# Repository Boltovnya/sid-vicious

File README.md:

# SID Vicious

SID Vicious is an open source breakout board for the MOS 6582/8580 Sound Interface Device.

## Images

### PCB Front

### PCB Rear

## Schematic

The schematic for SID Vicious can be found [here](pdfs/SID%20Tester.pdf)

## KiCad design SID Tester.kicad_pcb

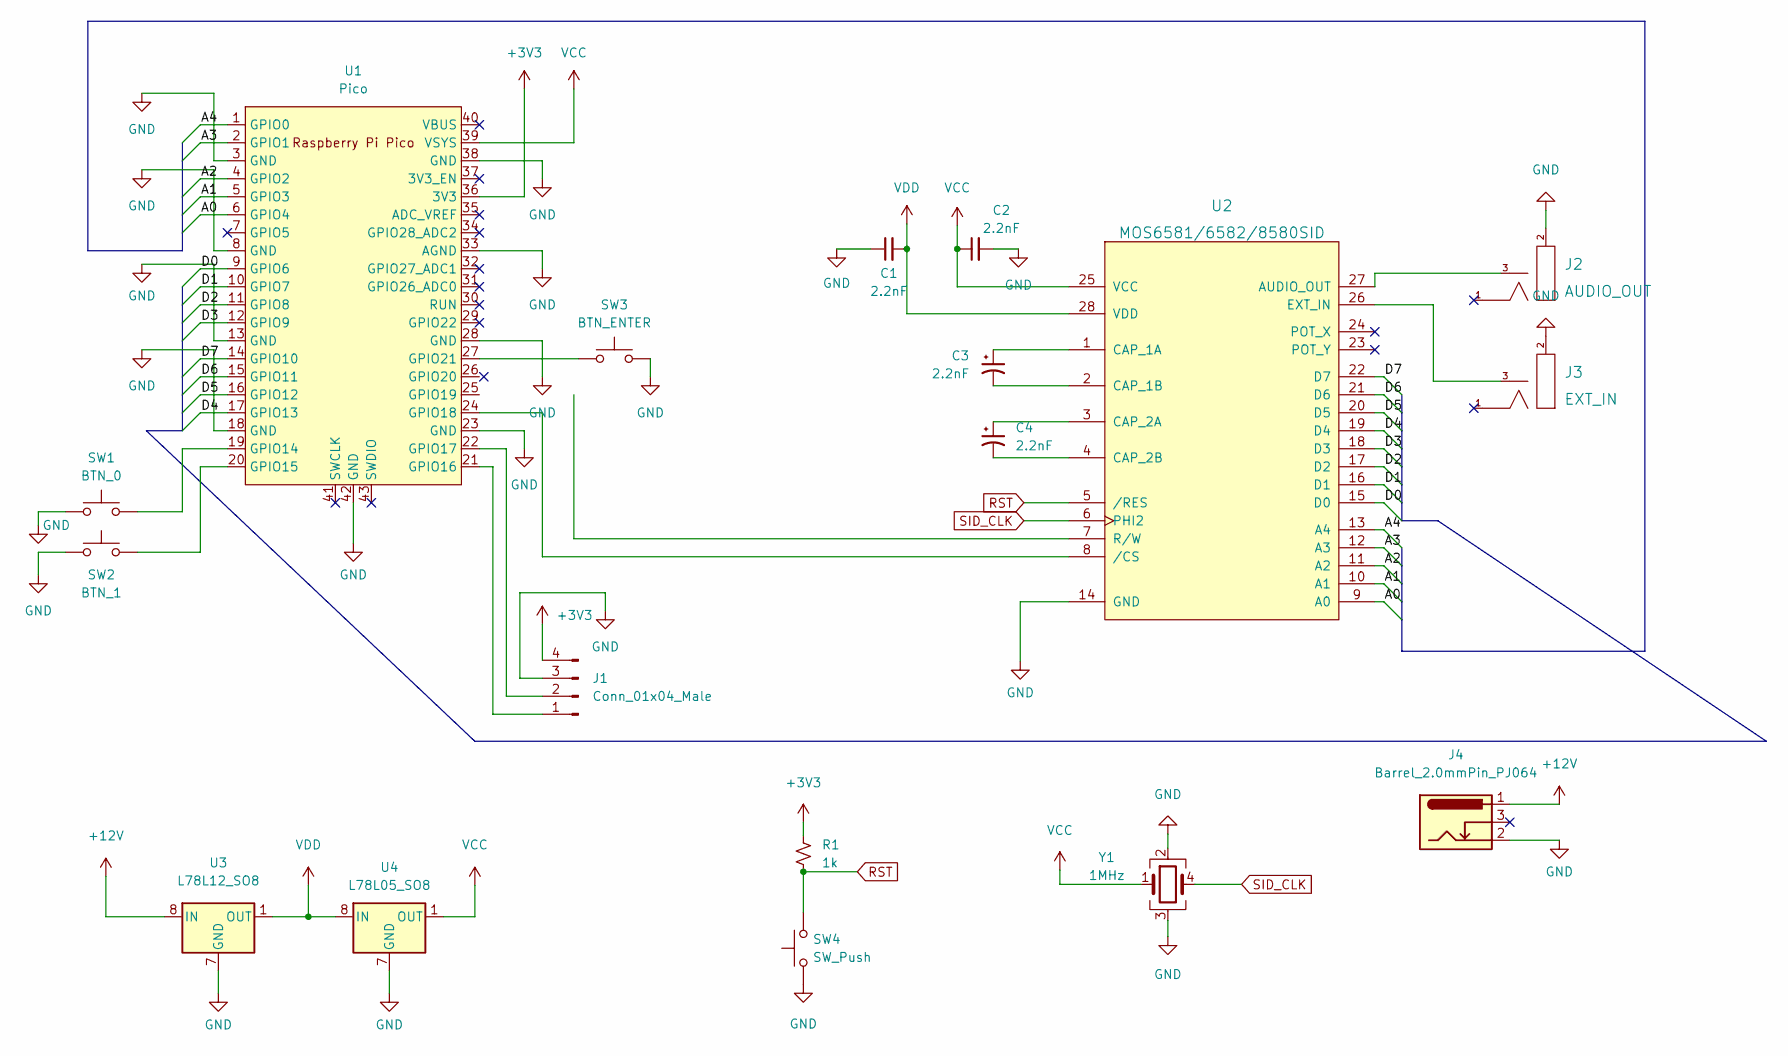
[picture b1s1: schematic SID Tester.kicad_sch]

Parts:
C1, C2: 2.2nF; C_0603_1608Metric
C3, C4: 2.2nF; CP_Elec_4x3
J1: Conn_01x04_Male; PinHeader_1x04_P1.27mm_Vertical
J2: AUDIO_OUT; EighthInch_PJ398SM; Part Number WQP-WQP518MA
J3: EXT_IN; EighthInch_PJ398SM; Part Number WQP-WQP518MA
J4: Barrel_2.0mmPin_PJ064; Barrel_Vert_PJ064_slotted; Part Number WQP-DC026M (2.0mm center pin)
R1: 1k; R_0603_1608Metric
SW1: BTN_0; SW_Cherry_MX_1.00u_PCB
SW2: BTN_1; SW_Cherry_MX_1.00u_PCB
SW3: BTN_ENTER; SW_Cherry_MX_1.00u_PCB
SW4: SW_Push; SW_SPST_EVQQ2
U1: Pico; RPi_Pico_SMD_TH
U2: MOS6581/6582/8580SID; DIP-28_W15.24mm_Socket
U3: L78L12_SO8; SOIC-8_3.9x4.9mm_P1.27mm
U4: L78L05_SO8; SOIC-8_3.9x4.9mm_P1.27mm
Y1: 1MHz; Crystal_SMD_TXC_7M-4Pin_3.2x2.5mm

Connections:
+3V3: J1.4, R1.1, U1.36 (3V3)
+12V: J4.1, U3.8 (IN)
/A0: U1.6 (GPIO4), U2.9 (A0)
/A1: U1.5 (GPIO3), U2.10 (A1)
/A2: U1.4 (GPIO2), U2.11 (A2)
/A3: U1.2 (GPIO1), U2.12 (A3)
/A4: U1.1 (GPIO0), U2.13 (A4)
/D0: U1.9 (GPIO6), U2.15 (D0)
/D1: U1.10 (GPIO7), U2.16 (D1)
/D2: U1.11 (GPIO8), U2.17 (D2)
/D3: U1.12 (GPIO9), U2.18 (D3)
/D4: U1.17 (GPIO13), U2.19 (D4)
/D5: U1.16 (GPIO12), U2.20 (D5)
/D6: U1.15 (GPIO11), U2.21 (D6)
/D7: U1.14 (GPIO10), U2.22 (D7)
GND: C1.1, C2.2, J1.3, J2.2 (SHEILD), J3.2 (SHEILD), J4.2, SW1.1, SW2.1, SW3.2, SW4.1, U1.3 (GND), U1.8 (GND), U1.13 (GND), U1.18 (GND), U1.23 (GND), U1.28 (GND), U1.33 (AGND), U1.38 (GND), U1.42 (GND), U2.14 (GND), U3.2 (GND), U3.3 (GND), U3.6 (GND), U3.7 (GND), U4.2 (GND), U4.3 (GND), U4.6 (GND), U4.7 (GND), Y1.2, Y1.3
unnamed: C3.1, U2.1 (CAP_1A)
unnamed: C3.2, U2.2 (CAP_1B)
unnamed: C4.1, U2.3 (CAP_2A)
unnamed: C4.2, U2.4 (CAP_2B)
unnamed: SW1.2, U1.19 (GPIO14)
unnamed: SW2.2, U1.20 (GPIO15)
unnamed: SW3.1, U1.27 (GPIO21)
unnamed: J1.1, U1.21 (GPIO16)
unnamed: J1.2, U1.22 (GPIO17)
unnamed: U1.24 (GPIO18), U2.8 (/CS)
unnamed: U1.25 (GPIO19), U2.7 (R/W)
unnamed: J3.3 (SW), U2.26 (EXT_IN)
unnamed: J2.3 (SW), U2.27 (AUDIO_OUT)
RST: R1.2, SW4.2, U2.5 (/RES)
SID_CLK: U2.6 (PHI2), Y1.4
VCC: C2.1, U1.39 (VSYS), U2.25 (VCC), U4.1 (OUT), Y1.1
VDD: C1.2, U2.28 (VDD), U3.1 (OUT), U4.8 (IN)

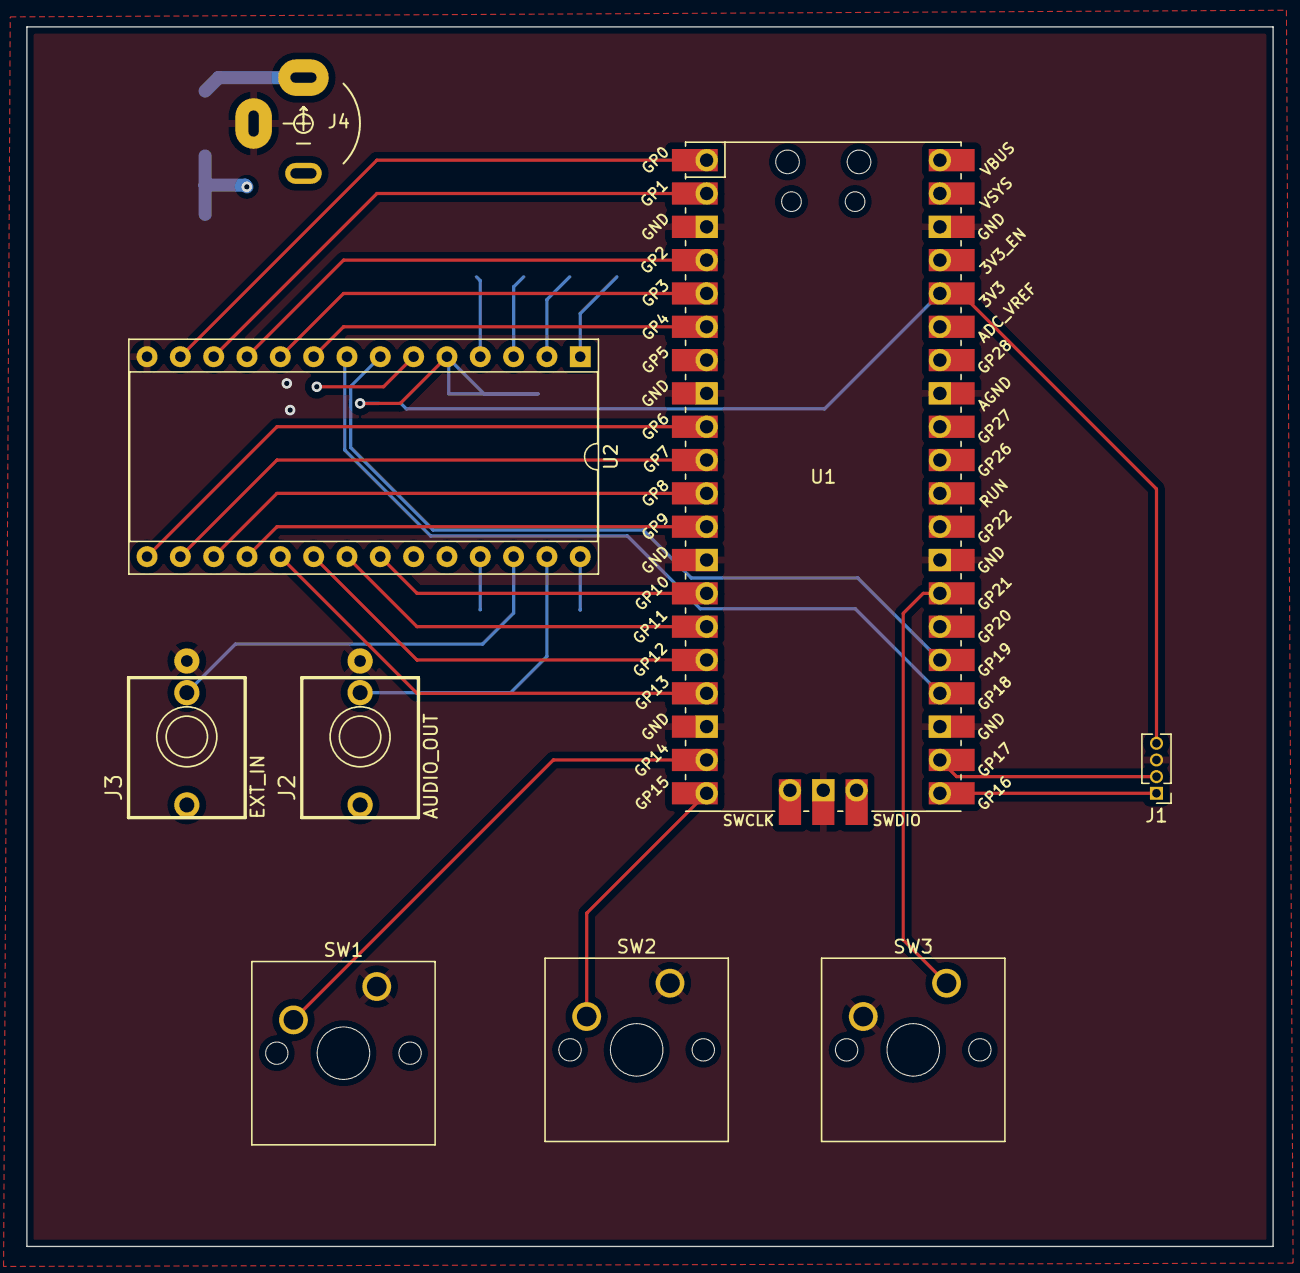
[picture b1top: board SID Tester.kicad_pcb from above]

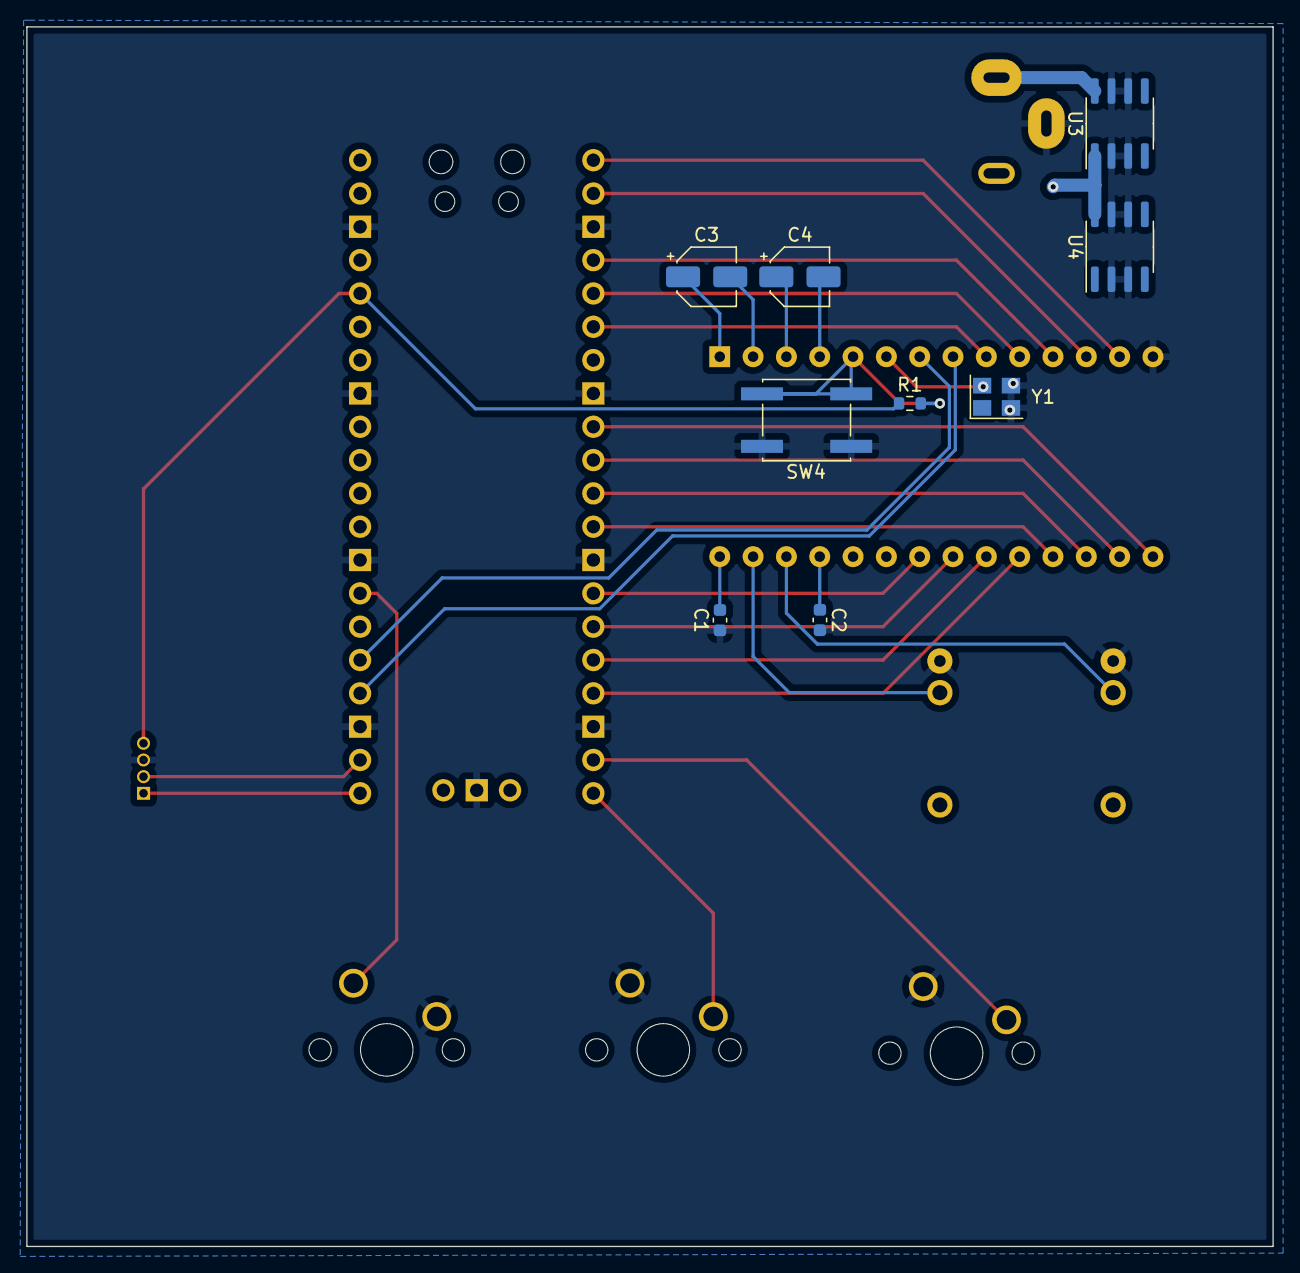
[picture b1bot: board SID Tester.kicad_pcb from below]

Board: 4 copper layers, 95.0 x 93.0 mm, 18 parts (9 on the bottom side), 33 nets.

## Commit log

2022-12-30 Fixed screen logic
